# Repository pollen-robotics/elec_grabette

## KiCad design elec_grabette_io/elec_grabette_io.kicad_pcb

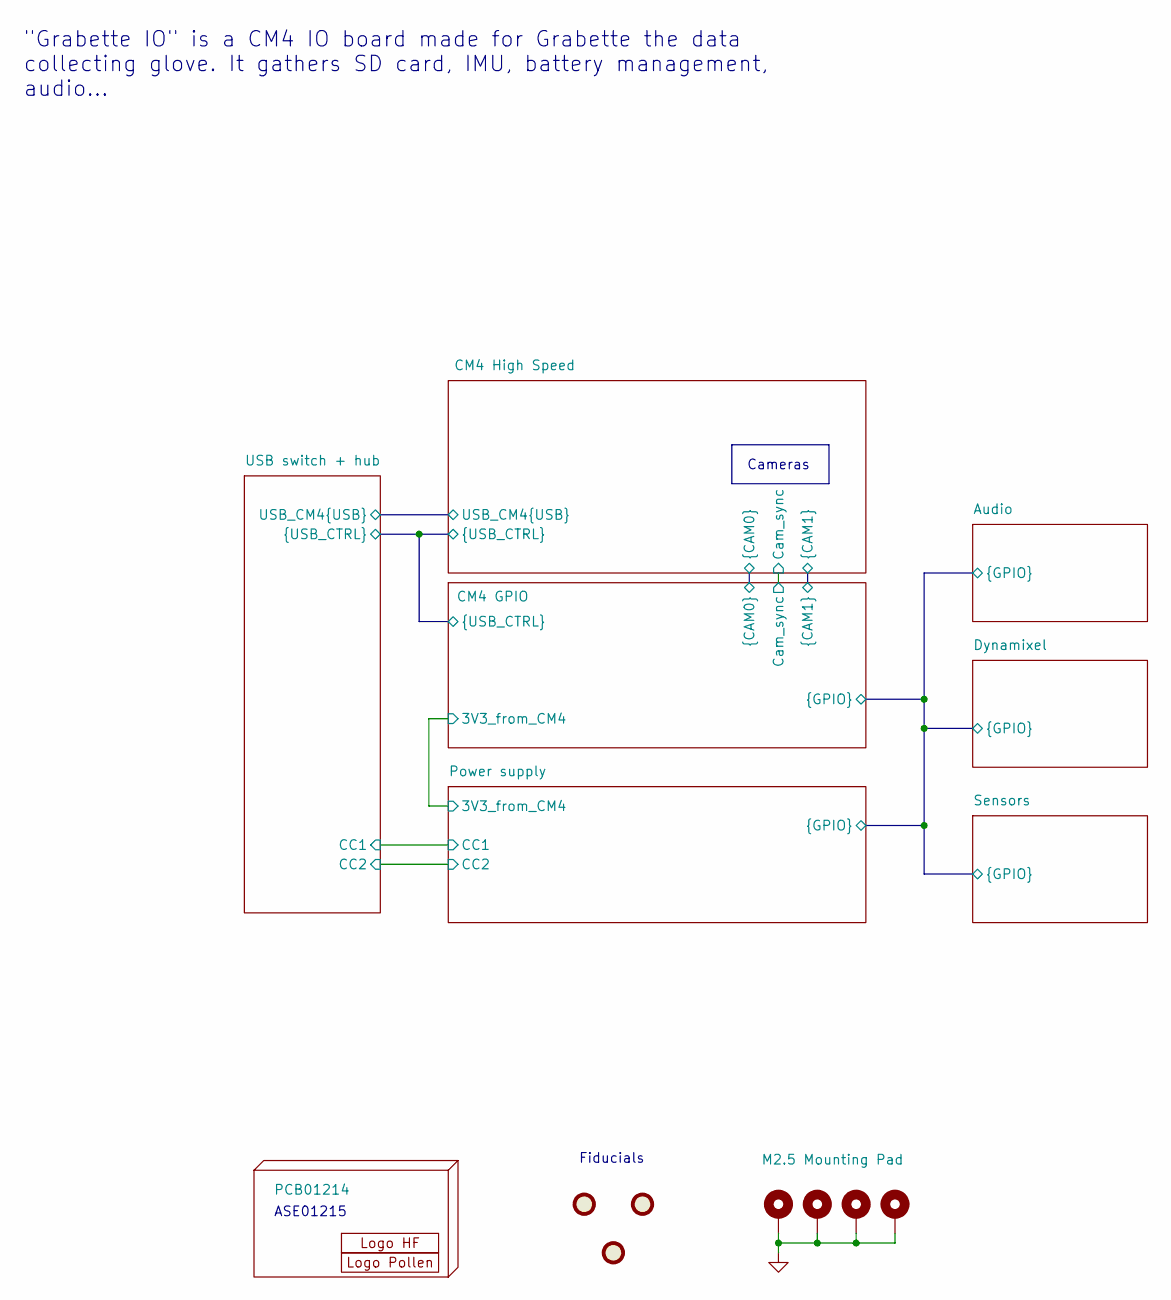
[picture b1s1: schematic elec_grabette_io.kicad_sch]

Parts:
FID1, FID2, FID3: DNP Fiducial; Fiducial_1mm_Mask2mm
H1: PCB01214
H2: Logo HF 2025; Logo_HF_2025
H3: DNP Logo Pollen 2021; Logo_Pollen_2021_sq
H4, H5, H6, H7: M2.5 Mounting Pad; MountingHole_2.7mm_M2.5_ISO7380_Pad_TopBottom

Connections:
GND: H4.1 (1_1), H5.1 (1_1), H6.1 (1_1), H7.1 (1_1); also elsewhere on the board

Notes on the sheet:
Fiducials
ASE01215
Cameras
"Grabette IO" is a CM4 IO board made for Grabette the data collecting glove. It gathers SD card, IMU, battery management, audio…

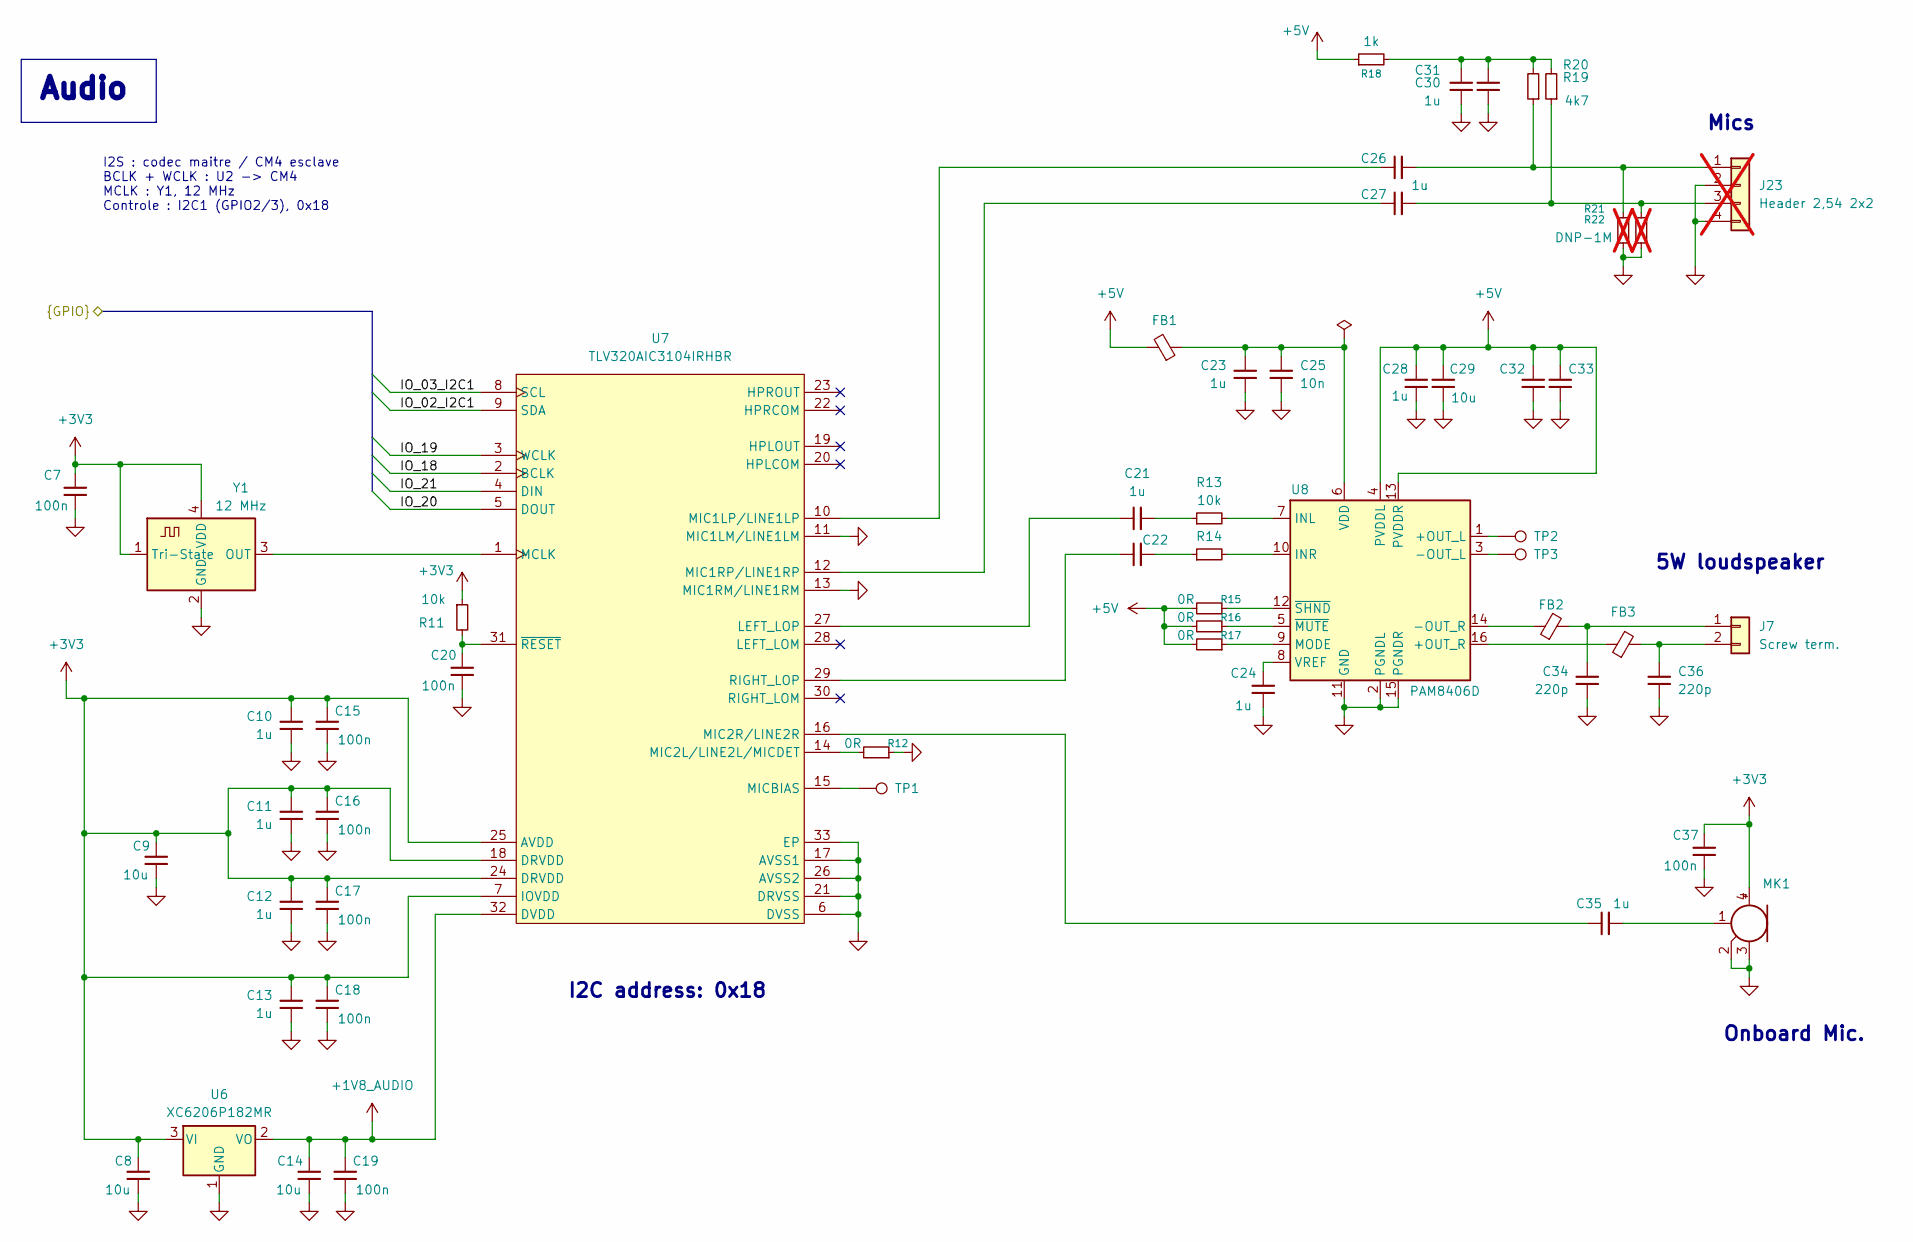
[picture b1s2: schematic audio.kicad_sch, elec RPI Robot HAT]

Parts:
C7, C15, C16, C17, C18, C19, C20, C37: 100n; C_0402_1005Metric; LCSC Part C307331
C8, C9, C14, C29, C33: 10u; C_0603_1608Metric; LCSC Part C1691
C10, C11, C12, C13, C21, C22, C23, C24, C26, C27, C28, C30, C31, C32, C35: 1u; C_0402_1005Metric; LCSC Part C52923
C25: 10n; C_0402_1005Metric; LCSC Part C15195
C34, C36: 220p; C_0402_1005Metric; LCSC Part C71693
FB1: 1.3A 600R@100MHz; L_0402_1005Metric; LCSC Part C76884
FB2, FB3: 2A - 120R@100MHz; L_0402_1005Metric; LCSC Part C88970
J7: Screw term.; CONN-TH_DB125-2.54-2P-GN; LCSC Part C918120
J23: Header 2,54 2x2; PinHeader_2x02_P2.54mm_Vertical; not fitted
MK1: Microphone_MEMS; MIC-SMD_4P-L2.8-W1.9-P1.84-TL; LCSC Part C7587901
R11, R13, R14: 10k; R_0402_1005Metric; LCSC Part C25744
R12, R15, R16, R17: 0R; R_0402_1005Metric; LCSC Part C17168
R18: 1k; R_0402_1005Metric; LCSC Part C105637
R19, R20: 4k7; R_0402_1005Metric; LCSC Part C105871
R21, R22: DNP-1M; R_0402_1005Metric; not fitted
TP1, TP2, TP3: TestPoint; TestPoint_Loop_D2.50mm_Drill1.0mm_LowProfile
U6: XC6206P182MR; SOT-23-3; LCSC Part C347373
U7: TLV320AIC3104IRHBR; VQFN-32-1EP_5x5mm_P0.5mm_EP3.5x3.5mm; LCSC Part C181753
U8: PAM8406D; SOIC-16_3.9x9.9mm_P1.27mm; LCSC Part C86270
Y1: 12 MHz; Oscillator_SMD_Abracon_ASDMB-4Pin_2.5x2.0mm; LCSC Part C7425459

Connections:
+1V8_AUDIO: C14.1, C19.2, U6.2 (VO), U7.32 (DVDD)
+3V3: C7.2, C8.1, C9.1, C10.2, C11.2, C12.2, C13.2, C15.2, C16.2, C17.2, C18.2, C37.2, MK1.4 (+), R11.1, U6.3 (VI), U7.7 (IOVDD), U7.18 (DRVDD), U7.24 (DRVDD), U7.25 (AVDD), Y1.1 (Tri-State), Y1.4 (VDD); also elsewhere on the board
+5V: C28.1, C29.1, C32.1, C33.1, FB1.2, R15.2, R16.2, R17.2, R18.1, U8.4 (PVDDL), U8.13 (PVDDR); also elsewhere on the board
/Audio/IO_02_I2C1: U7.9 (SDA); also elsewhere on the board
/Audio/IO_03_I2C1: U7.8 (SCL); also elsewhere on the board
/Audio/IO_18: U7.2 (BCLK); also elsewhere on the board
/Audio/IO_19: U7.3 (WCLK); also elsewhere on the board
/Audio/IO_20: U7.5 (DOUT); also elsewhere on the board
/Audio/IO_21: U7.4 (DIN); also elsewhere on the board
GND: C7.1, C8.2, C9.2, C10.1, C11.1, C12.1, C13.1, C14.2, C15.1, C16.1, C17.1, C18.1, C19.1, C20.1, C23.2, C24.1, C25.2, C28.2, C29.2, C30.1, C31.1, C32.2, C33.2, C34.2, C36.2, C37.1, J23.2, J23.4, MK1.2 (-), MK1.3 (-), R12.1, R21.1, R22.1, U6.1 (GND), U7.6 (DVSS), U7.11 (MIC1LM/LINE1LM), U7.13 (MIC1RM/LINE1RM), U7.17 (AVSS1), U7.21 (DRVSS), U7.26 (AVSS2), U7.33 (EP), U8.2 (PGNDL), U8.11 (GND), U8.15 (PGNDR), Y1.2 (GND); also elsewhere on the board
unnamed: C21.2, R13.1
unnamed: C22.2, R14.1
unnamed: C30.2, C31.2, R18.2, R19.2, R20.2
unnamed: C35.1, MK1.1 (-)
unnamed: C34.1, FB2.2, J7.1
unnamed: C36.1, FB3.2, J7.2
unnamed: C26.2, J23.1, R19.1, R21.2
unnamed: C27.2, J23.3, R20.1, R22.2
unnamed: C21.1, U7.27 (LEFT_LOP)
unnamed: U7.1 (MCLK), Y1.3 (OUT)
unnamed: C26.1, U7.10 (MIC1LP/LINE1LP)
unnamed: C27.1, U7.12 (MIC1RP/LINE1RP)
unnamed: R12.2, U7.14 (MIC2L/LINE2L/MICDET)
unnamed: C35.2, U7.16 (MIC2R/LINE2R)
unnamed: TP1.1 (1_1), U7.15 (MICBIAS)
unnamed: C22.1, U7.29 (RIGHT_LOP)
unnamed: C20.2, R11.2, U7.31 (~RESET)
unnamed: TP2.1 (1_1), U8.1 (+OUT_L)
unnamed: FB3.1, U8.16 (+OUT_R)
unnamed: TP3.1 (1_1), U8.3 (-OUT_L)
unnamed: FB2.1, U8.14 (-OUT_R)
unnamed: R13.2, U8.7 (INL)
unnamed: R14.2, U8.10 (INR)
unnamed: R17.1, U8.9 (MODE)
unnamed: C23.1, C25.1, FB1.1, U8.6 (VDD)
unnamed: C24.2, U8.8 (VREF)
unnamed: R16.1, U8.5 (~MUTE)
unnamed: R15.1, U8.12 (~SHND)

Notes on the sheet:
Onboard Mic.
5W loudspeaker
Mics
I2S : codec maitre / CM4 esclave BCLK + WCLK : U2 -> CM4 MCLK : Y1, 12 MHz Controle : I2C1 (GPIO2/3), 0x18
I2C address: 0x18
Audio

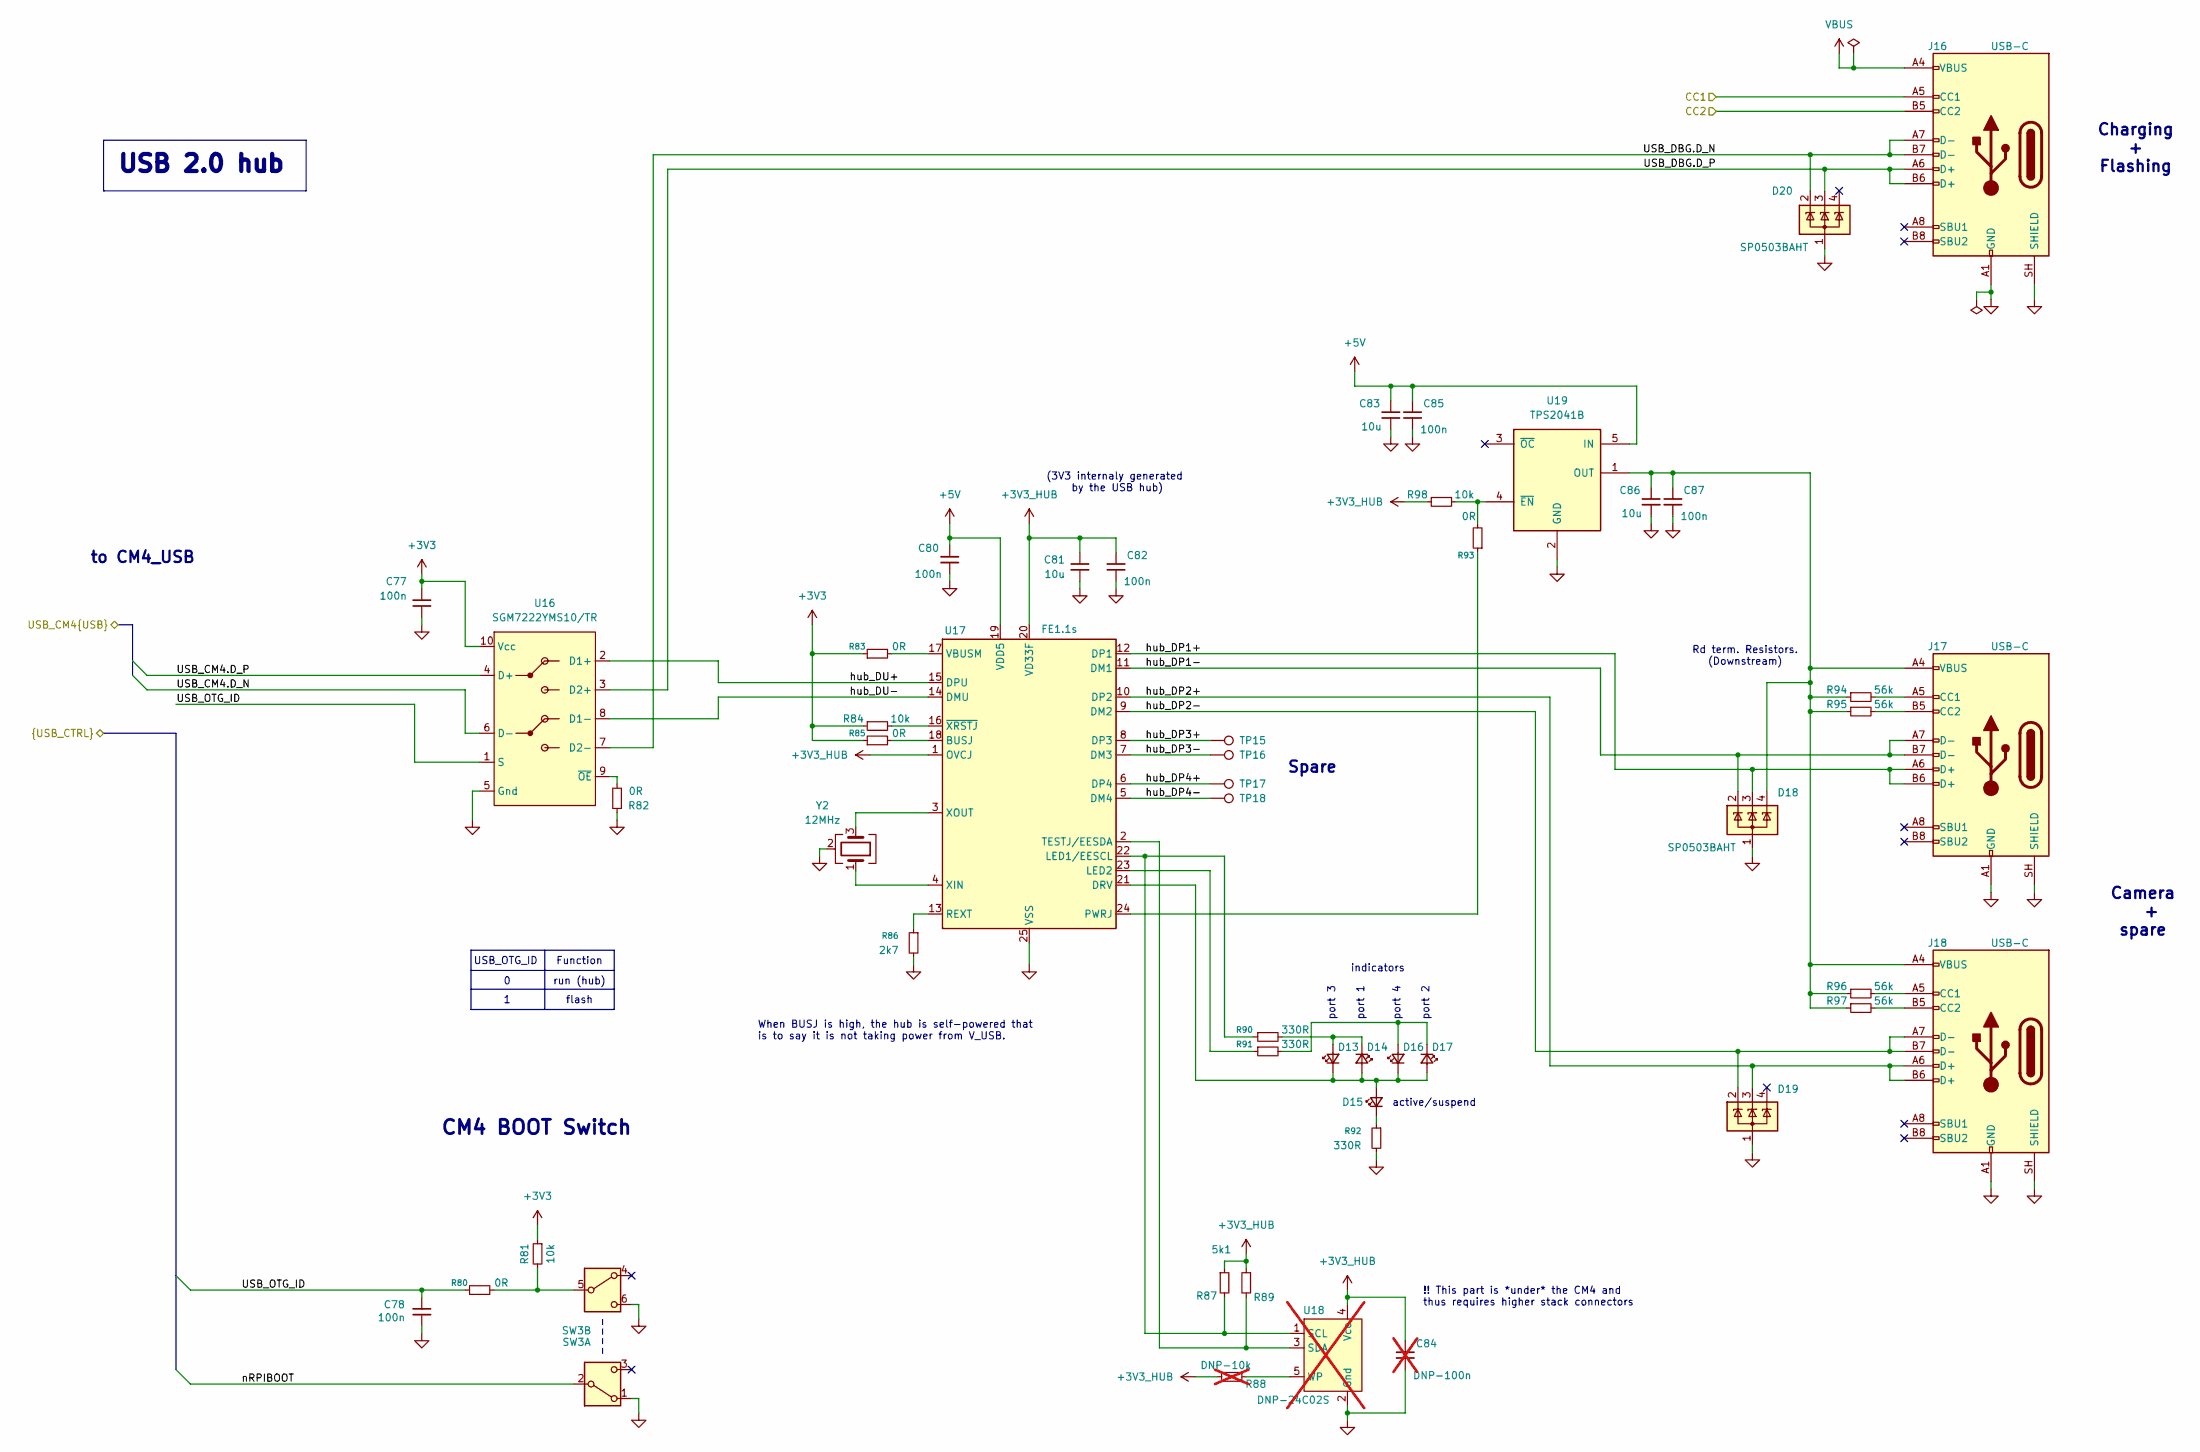
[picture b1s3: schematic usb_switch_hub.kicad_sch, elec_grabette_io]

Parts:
C77, C78: 100n; C_0402_1005Metric; Voltage Rating 16V; MPN CC0402KRX7R7BB104; LCSC Part C307331
C80, C82, C85, C87: 100n; C_0402_1005Metric; LCSC Part C307331
C81, C83, C86: 10u; C_0603_1608Metric; LCSC Part C1691
C84: DNP-100n; C_0402_1005Metric; not fitted
D13, D14, D15, D16, D17: LED_Small; LED_0603_1608Metric; LCSC Part C7429915
D18, D19, D20: SP0503BAHT; SOT-143; LCSC Part C3040626
J16, J17, J18: USB-C; USB-C-SMD_TYPE-C-6PIN-2MD-073 Shou Han - C2765186; LCSC C2765186
R80, R83, R85, R93: 0R; R_0402_1005Metric; LCSC Part C17168
R81: 10k; R_0402_1005Metric; Power Rating 1%; MPN RC0402FR-0710KL; LCSC Part C25744
R82: 0R; R_0402_1005Metric; Power Rating 5%; MPN RC0402JR-070RL; LCSC Part C17168
R84, R98: 10k; R_0402_1005Metric; LCSC Part C25744
R86: 2k7; R_0402_1005Metric; LCSC Part C138017
R87, R89: 5k1; R_0402_1005Metric; LCSC Part C25905
R88: DNP-10k; R_0402_1005Metric; not fitted
R90, R91, R92: 330R; R_0402_1005Metric; LCSC Part C2906929
R94, R95, R96, R97: 56k; R_0402_1005Metric; LCSC C114756
SW3: SW_DPDT; SW-SMD_6P-L7.2-W3.5-P2.50-LS6.0-TL; LCSC Part C2837066
TP15, TP16, TP17, TP18: TestPoint; TestPoint_Pad_D1.0mm
U16: SGM7222YMS10/TR; MSOP-10_3x3mm_P0.5mm; MPN SGM7222YMS10/TR; LCSC Part C113292
U17: FE1.1s; WQFN-24-1EP_4x4mm_P0.5mm_EP2.6x2.6mm; LCSC Part C6776948
U18: DNP-24C02S; SOT-23-5; not fitted
U19: TPS2041B; SOT-23-5; LCSC Part C51386
Y2: 12MHz; Crystal_SMD_3225-4Pin_3.2x2.5mm; LCSC Part C133334

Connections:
+3V3: C77.1, R81.1, R83.1, R84.1, R85.1, U16.10 (Vcc); also elsewhere on the board
+3V3_HUB: C81.1, C82.2, C84.2, R87.1, R88.2, R89.1, R98.1, U17.1 (OVCJ), U17.20 (VD33F), U18.4 (Vcc)
+5V: C80.2, C83.1, C85.2, U17.19 (VDD5), U19.5 (IN); also elsewhere on the board
/CM4 GPIO/USB_OTG_ID: C78.2, R80.1, U16.1 (S); also elsewhere on the board
/CM4 GPIO/nRPIBOOT: SW3.2 (B); also elsewhere on the board
/CM4 High Speed/USB_CM4.D_N: U16.6 (D-); also elsewhere on the board
/CM4 High Speed/USB_CM4.D_P: U16.4 (D+); also elsewhere on the board
/Power supply/CC1: J16.A5 (CC1); also elsewhere on the board
/Power supply/CC2: J16.B5 (CC2); also elsewhere on the board
/USB switch + hub/USB_DBG.D_N: D20.2 (K), J16.A7 (D-), J16.B7 (D-), U16.7 (D2-)
/USB switch + hub/USB_DBG.D_P: D20.3 (K), J16.A6 (D+), J16.B6 (D+), U16.3 (D2+)
/USB switch + hub/hub_DP1+: D18.3 (K), J17.A6 (D+), J17.B6 (D+), U17.12 (DP1)
/USB switch + hub/hub_DP1-: D18.2 (K), J17.A7 (D-), J17.B7 (D-), U17.11 (DM1)
/USB switch + hub/hub_DP2+: D19.3 (K), J18.A6 (D+), J18.B6 (D+), U17.10 (DP2)
/USB switch + hub/hub_DP2-: D19.2 (K), J18.A7 (D-), J18.B7 (D-), U17.9 (DM2)
/USB switch + hub/hub_DP3+: TP15.1 (1_1), U17.8 (DP3)
/USB switch + hub/hub_DP3-: TP16.1 (1_1), U17.7 (DM3)
/USB switch + hub/hub_DP4+: TP17.1 (1_1), U17.6 (DP4)
/USB switch + hub/hub_DP4-: TP18.1 (1_1), U17.5 (DM4)
/USB switch + hub/hub_DU+: U16.2 (D1+), U17.15 (DPU)
/USB switch + hub/hub_DU-: U16.8 (D1-), U17.14 (DMU)
GND: C77.2, C78.1, C80.1, C81.2, C82.1, C83.2, C84.1, C85.1, C86.2, C87.1, D18.1 (A), D19.1 (A), D20.1 (A), J16.A1 (GND), J16.A12 (GND), J16.B1 (GND), J16.B12 (GND), J16.SH (SHIELD), J17.A1 (GND), J17.A12 (GND), J17.B1 (GND), J17.B12 (GND), J17.SH (SHIELD), J18.A1 (GND), J18.A12 (GND), J18.B1 (GND), J18.B12 (GND), J18.SH (SHIELD), R82.1, R86.2, R92.2, SW3.1 (A), SW3.6 (C), U16.5 (Gnd), U17.25 (VSS), U18.2 (Gnd), U19.2 (GND), Y2.2 (G), Y2.4 (G); also elsewhere on the board
unnamed: D13.2 (A), D14.1 (K), R90.2
unnamed: D13.1 (K), D14.2 (A), D15.2 (A), D16.1 (K), D17.2 (A), U17.21 (DRV)
unnamed: D15.1 (K), R92.1
unnamed: D16.2 (A), D17.1 (K), R91.2
unnamed: J17.A5 (CC1), R94.2
unnamed: J17.B5 (CC2), R95.2
unnamed: J18.A5 (CC1), R96.2
unnamed: J18.B5 (CC2), R97.2
unnamed: R80.2, R81.2, SW3.5 (B)
unnamed: R82.2, U16.9 (~OE)
unnamed: R85.2, U17.18 (BUSJ)
unnamed: R87.2, R90.1, U17.22 (LED1/EESCL), U18.1 (SCL)
unnamed: R91.1, U17.23 (LED2)
unnamed: R93.1, U17.24 (PWRJ)
unnamed: R86.1, U17.13 (REXT)
unnamed: R89.2, U17.2 (TESTJ/EESDA), U18.3 (SDA)
unnamed: R83.2, U17.17 (VBUSM)
unnamed: U17.4 (XIN), Y2.1
unnamed: U17.3 (XOUT), Y2.3
unnamed: R84.2, U17.16 (~XRSTJ)
unnamed: R88.1, U18.5 (WP)
unnamed: C86.1, C87.2, D18.4 (K), J17.A4 (VBUS), J17.A9 (VBUS), J17.B4 (VBUS), J17.B9 (VBUS), J18.A4 (VBUS), J18.A9 (VBUS), J18.B4 (VBUS), J18.B9 (VBUS), R94.1, R95.1, R96.1, R97.1, U19.1 (OUT)
unnamed: R93.2, R98.2, U19.4 (~EN)
VBUS: J16.A4 (VBUS), J16.A9 (VBUS), J16.B4 (VBUS), J16.B9 (VBUS); also elsewhere on the board

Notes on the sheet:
Camera + spare
port 4
When BUSJ is high, the hub is self-powered that is to say it is not taking power from V_USB.
run (hub)
USB_OTG_ID
indicators
port 2
port 3
CM4 BOOT Switch
flash
Spare
(3V3 internaly generated by the USB hub)
Rd term. Resistors. (Downstream)
!! This part is *under* the CM4 and thus requires higher stack connectors
Function
port 1
active/suspend
to CM4_USB
Charging + Flashing
USB 2.0 hub

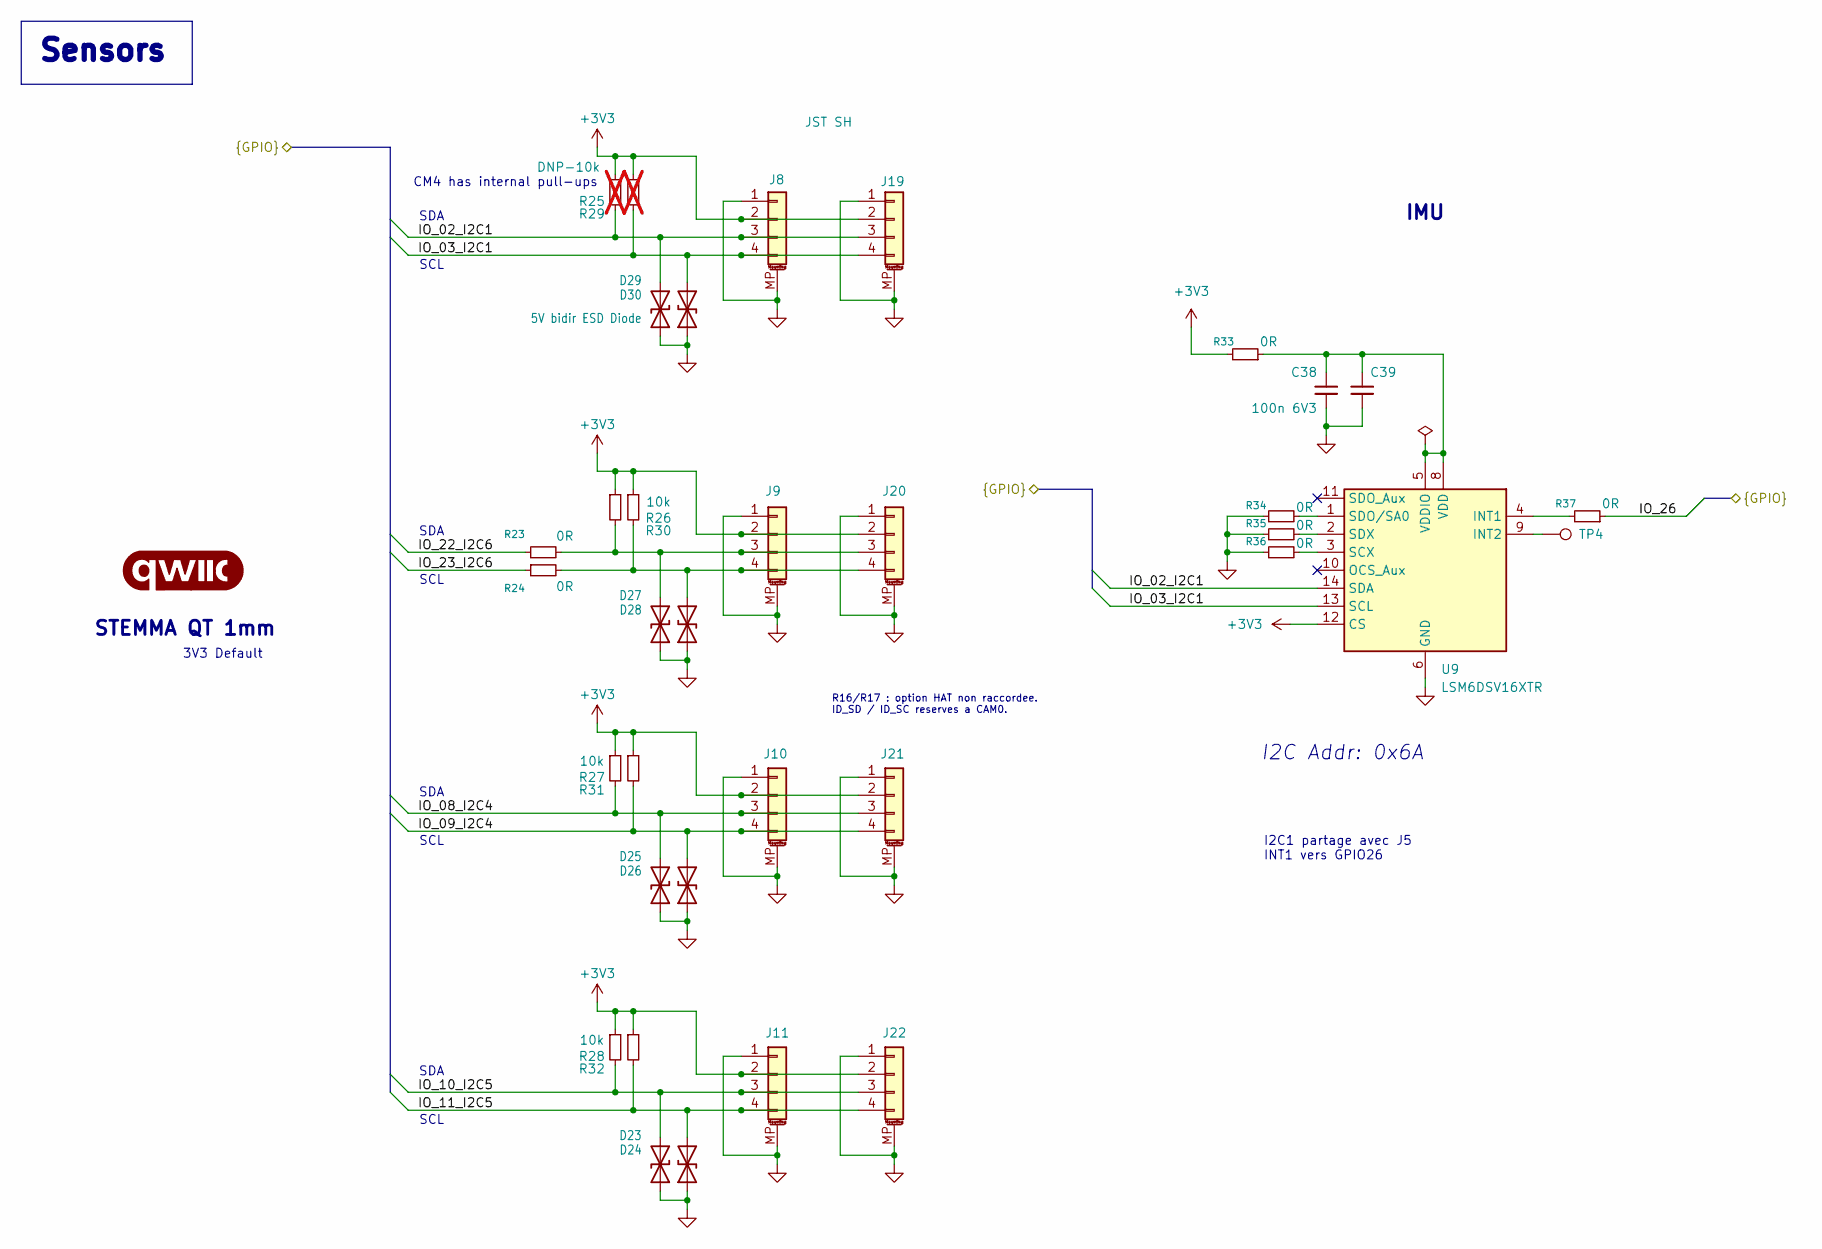
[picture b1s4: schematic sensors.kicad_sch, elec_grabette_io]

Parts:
C38, C39: 100n 6V3; C_0402_1005Metric; LCSC Part C1525
D23, D24, D25, D26, D27, D28, D29, D30: 5V bidir ESD Diode; D_0402_1005Metric; LCSC Part C48260
G1: qwiic_Logo; Logo_qwiic_5mm
J8, J9, J10, J11, J19, J20, J21, J22: JST SH; JST_SH_BM04B-SRSS-TB_1x04-1MP_P1.00mm_Vertical; LCSC Part C51940129
R23, R24, R33, R34, R35, R36, R37: 0R; R_0402_1005Metric; LCSC Part C17168
R25, R29: DNP-10k; R_0402_1005Metric; not fitted
R26, R27, R28, R30, R31, R32: 10k; R_0402_1005Metric; LCSC Part C25744
TP4: TestPoint; TestPoint_Pad_D1.0mm
U9: LSM6DSV16XTR; LGA-14_3x2.5mm_P0.5mm_LayoutBorder3x4y; LCSC Part C5267406

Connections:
+3V3: J8.2, J9.2, J10.2, J11.2, J19.2, J20.2, J21.2, J22.2, R25.1, R26.1, R27.1, R28.1, R29.1, R30.1, R31.1, R32.1, R33.2, U9.12 (CS); also elsewhere on the board
/Audio/IO_02_I2C1: D29.2 (A2), J8.3, J19.3, R25.2, U9.14 (SDA); also elsewhere on the board
/Audio/IO_03_I2C1: D30.2 (A2), J8.4, J19.4, R29.2, U9.13 (SCL); also elsewhere on the board
/Audio/IO_08_I2C4: D25.2 (A2), J10.3, J21.3, R27.2; also elsewhere on the board
/Audio/IO_09_I2C4: D26.2 (A2), J10.4, J21.4, R31.2; also elsewhere on the board
/Audio/IO_10_I2C5: D23.2 (A2), J11.3, J22.3, R28.2; also elsewhere on the board
/Audio/IO_11_I2C5: D24.2 (A2), J11.4, J22.4, R32.2; also elsewhere on the board
/Audio/IO_22_I2C6: R23.1; also elsewhere on the board
/Audio/IO_23_I2C6: R24.1; also elsewhere on the board
/Audio/IO_26: R37.1; also elsewhere on the board
GND: C38.2, C39.1, D23.1 (A1), D24.1 (A1), D25.1 (A1), D26.1 (A1), D27.1 (A1), D28.1 (A1), D29.1 (A1), D30.1 (A1), J8.1, J8.MP (MountPin), J9.1, J9.MP (MountPin), J10.1, J10.MP (MountPin), J11.1, J11.MP (MountPin), J19.1, J19.MP (MountPin), J20.1, J20.MP (MountPin), J21.1, J21.MP (MountPin), J22.1, J22.MP (MountPin), R34.1, R35.1, R36.1, U9.6 (GND), U9.7 (GND); also elsewhere on the board
unnamed: D27.2 (A2), J9.3, J20.3, R23.2, R26.2
unnamed: D28.2 (A2), J9.4, J20.4, R24.2, R30.2
unnamed: R37.2, U9.4 (INT1)
unnamed: TP4.1 (1_1), U9.9 (INT2)
unnamed: R36.2, U9.3 (SCX)
unnamed: R34.2, U9.1 (SDO/SA0)
unnamed: R35.2, U9.2 (SDX)
unnamed: C38.1, C39.2, R33.1, U9.5 (VDDIO), U9.8 (VDD)

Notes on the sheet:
SCL
STEMMA QT 1mm
SDA
3V3 Default
IMU
I2C Addr: 0x6A
R16/R17 : option HAT non raccordee. ID_SD / ID_SC reserves a CAM0.
I2C1 partage avec J5 INT1 vers GPIO26
CM4 has internal pull-ups
Sensors

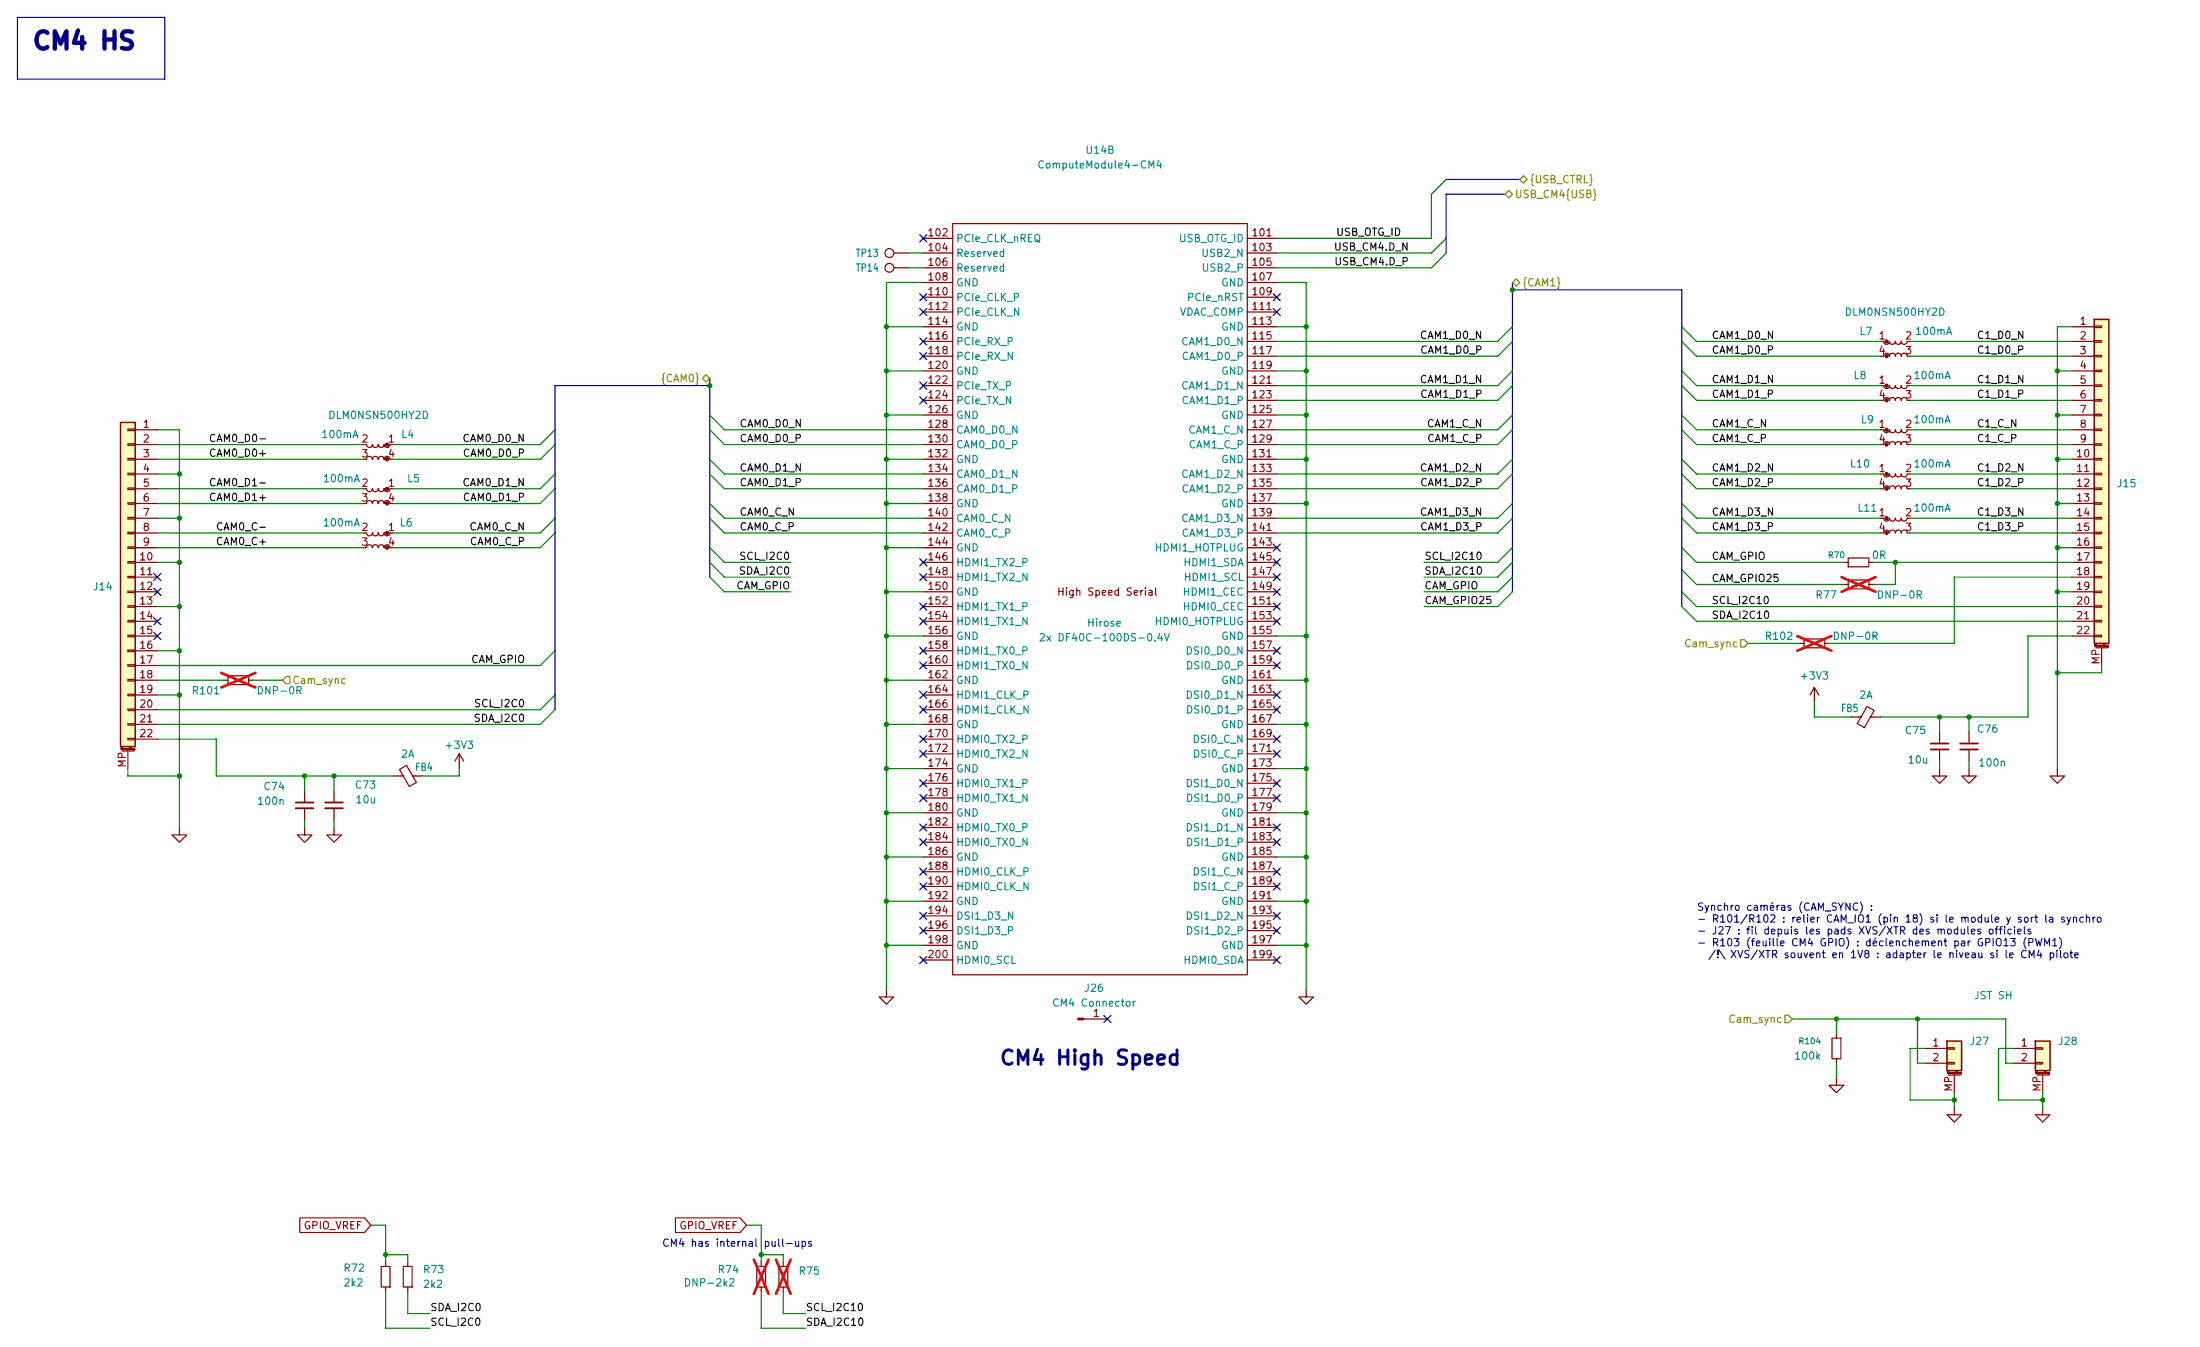
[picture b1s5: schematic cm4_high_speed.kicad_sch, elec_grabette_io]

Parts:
C73, C75: 10u; C_0603_1608Metric; Voltage Rating 10V; MPN CC0603KRX5R6BB106; LCSC Part C1691
C74, C76: 100n; C_0402_1005Metric; Voltage Rating 16V; MPN CC0402KRX7R7BB104; LCSC Part C307331
FB4, FB5: 2A - 120R@100MHz; L_0402_1005Metric; Rating 2A; MPN BLM18PG121SN1D; LCSC Part C88970
J14, J15: FPC Camera; FPC-SMD_AFC07-S22ECA-00; LCSC Part C262642
J26: CM4 Connector; position_only; LCSC Part C597931
J27, J28: JST SH; JST_SH_SM02B-SRSS-TB_1x02-1MP_P1.00mm_Horizontal; MPN BM02B-SRSS-TB(LF)(SN); LCSC Part C160402
L4, L5, L6, L7, L8, L9, L10, L11: DLM0NSN500HY2D; FILTER-SMD_4P-L0.8-W0.6-TL_DLP0NSC280HL2L; Rating 100mA; MPN DLM0NSN500HY2D; LCSC Part C913480
R70: 0R; R_0402_1005Metric; LCSC Part C17168
R72, R73: 2k2; R_0402_1005Metric; Power Rating 1%; MPN RC0402FR-072K2L; LCSC Part C2906865
R74, R75: DNP-2k2; R_0402_1005Metric; not fitted
R77, R101, R102: DNP-0R; R_0402_1005Metric; Power Rating 5%; MPN RC0402JR-070RL; LCSC Part C17168; not fitted
R104: 100k; R_0402_1005Metric; LCSC Part C22369186
TP13, TP14: TestPoint; TestPoint_Pad_D1.0mm; Part Type Test Point
U14: ComputeModule4-CM4; Raspberry-Pi-4-Compute-Module

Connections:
+3V3: FB4.1, FB5.1; also elsewhere on the board
/Audio/IO_25: R77.1; also elsewhere on the board
/CM4 GPIO/CAM0_C_N: L6.1, U14.140 (CAM0_C_N)
/CM4 GPIO/CAM0_C_P: L6.4, U14.142 (CAM0_C_P)
/CM4 GPIO/CAM0_D0_N: L4.1, U14.128 (CAM0_D0_N)
/CM4 GPIO/CAM0_D0_P: L4.4, U14.130 (CAM0_D0_P)
/CM4 GPIO/CAM0_D1_N: L5.1, U14.134 (CAM0_D1_N)
/CM4 GPIO/CAM0_D1_P: L5.4, U14.136 (CAM0_D1_P)
/CM4 GPIO/CAM1_C_N: L9.1, U14.127 (CAM1_C_N)
/CM4 GPIO/CAM1_C_P: L9.4, U14.129 (CAM1_C_P)
/CM4 GPIO/CAM1_D0_N: L7.1, U14.115 (CAM1_D0_N)
/CM4 GPIO/CAM1_D0_P: L7.4, U14.117 (CAM1_D0_P)
/CM4 GPIO/CAM1_D1_N: L8.1, U14.121 (CAM1_D1_N)
/CM4 GPIO/CAM1_D1_P: L8.4, U14.123 (CAM1_D1_P)
/CM4 GPIO/CAM1_D2_N: L10.1, U14.133 (CAM1_D2_N)
/CM4 GPIO/CAM1_D2_P: L10.4, U14.135 (CAM1_D2_P)
/CM4 GPIO/CAM1_D3_N: L11.1, U14.139 (CAM1_D3_N)
/CM4 GPIO/CAM1_D3_P: L11.4, U14.141 (CAM1_D3_P)
/CM4 GPIO/CAM_GPIO: J14.17, R70.1; also elsewhere on the board
/CM4 GPIO/Cam_sync: J27.2, J28.2, R101.2, R102.1, R104.1; also elsewhere on the board
/CM4 GPIO/SCL_I2C0: J14.20, R72.1; also elsewhere on the board
/CM4 GPIO/SCL_I2C10: J15.20, R75.1; also elsewhere on the board
/CM4 GPIO/SDA_I2C0: J14.21, R73.1; also elsewhere on the board
/CM4 GPIO/SDA_I2C10: J15.21, R74.1; also elsewhere on the board
/CM4 GPIO/USB_OTG_ID: U14.101 (USB_OTG_ID); also elsewhere on the board
/CM4 High Speed/C1_C_N: J15.8, L9.2
/CM4 High Speed/C1_C_P: J15.9, L9.3
/CM4 High Speed/C1_D0_N: J15.2, L7.2
/CM4 High Speed/C1_D0_P: J15.3, L7.3
/CM4 High Speed/C1_D1_N: J15.5, L8.2
/CM4 High Speed/C1_D1_P: J15.6, L8.3
/CM4 High Speed/C1_D2_N: J15.11, L10.2
/CM4 High Speed/C1_D2_P: J15.12, L10.3
/CM4 High Speed/C1_D3_N: J15.14, L11.2
/CM4 High Speed/C1_D3_P: J15.15, L11.3
/CM4 High Speed/CAM0_C+: J14.9, L6.3
/CM4 High Speed/CAM0_C-: J14.8, L6.2
/CM4 High Speed/CAM0_D0+: J14.3, L4.3
/CM4 High Speed/CAM0_D0-: J14.2, L4.2
/CM4 High Speed/CAM0_D1+: J14.6, L5.3
/CM4 High Speed/CAM0_D1-: J14.5, L5.2
/CM4 High Speed/USB_CM4.D_N: U14.103 (USB2_N); also elsewhere on the board
/CM4 High Speed/USB_CM4.D_P: U14.105 (USB2_P); also elsewhere on the board
GND: C73.2, C74.2, C75.2, C76.2, J14.1, J14.4, J14.7, J14.10, J14.13, J14.16, J14.19, J14.MP (MountPin), J15.1, J15.4, J15.7, J15.10, J15.13, J15.16, J15.19, J15.MP (MountPin), J27.1, J27.MP (MountPin), J28.1, J28.MP (MountPin), R104.2, U14.107 (GND), U14.108 (GND), U14.113 (GND), U14.114 (GND), U14.119 (GND), U14.120 (GND), U14.125 (GND), U14.126 (GND), U14.131 (GND), U14.132 (GND), U14.137 (GND), U14.138 (GND), U14.144 (GND), U14.150 (GND), U14.155 (GND), U14.156 (GND), U14.161 (GND), U14.162 (GND), U14.167 (GND), U14.168 (GND), U14.173 (GND), U14.174 (GND), U14.179 (GND), U14.180 (GND), U14.185 (GND), U14.186 (GND), U14.191 (GND), U14.192 (GND), U14.197 (GND), U14.198 (GND); also elsewhere on the board
GPIO_VREF: R72.2, R73.2, R74.2, R75.2; also elsewhere on the board
unnamed: J14.18, R101.1
unnamed: C73.1, C74.1, FB4.2, J14.22
unnamed: J15.17, R70.2, R77.2
unnamed: J15.18, R102.2
unnamed: C75.1, C76.1, FB5.2, J15.22
unnamed: TP13.1 (1_1), U14.104 (Reserved)
unnamed: TP14.1 (1_1), U14.106 (Reserved)

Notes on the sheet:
CM4 has internal pull-ups
CM4 High Speed
Synchro caméras (CAM_SYNC) : - R101/R102 : relier CAM_IO1 (pin 18) si le module y sort la synchro - J27 : fil depuis les pads XVS/XTR des modules officiels - R103 (feuille CM4 GPIO) : déclenchement par GPIO13 (PWM1) /!\ XVS/XTR souvent en 1V8 : adapter le niveau si le CM4 pilote
CM4 HS
